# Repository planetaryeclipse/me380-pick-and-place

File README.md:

# me380-pick-and-place
Repository to contain documentation, firmware, and controls for the ME 380 pick and place robot.

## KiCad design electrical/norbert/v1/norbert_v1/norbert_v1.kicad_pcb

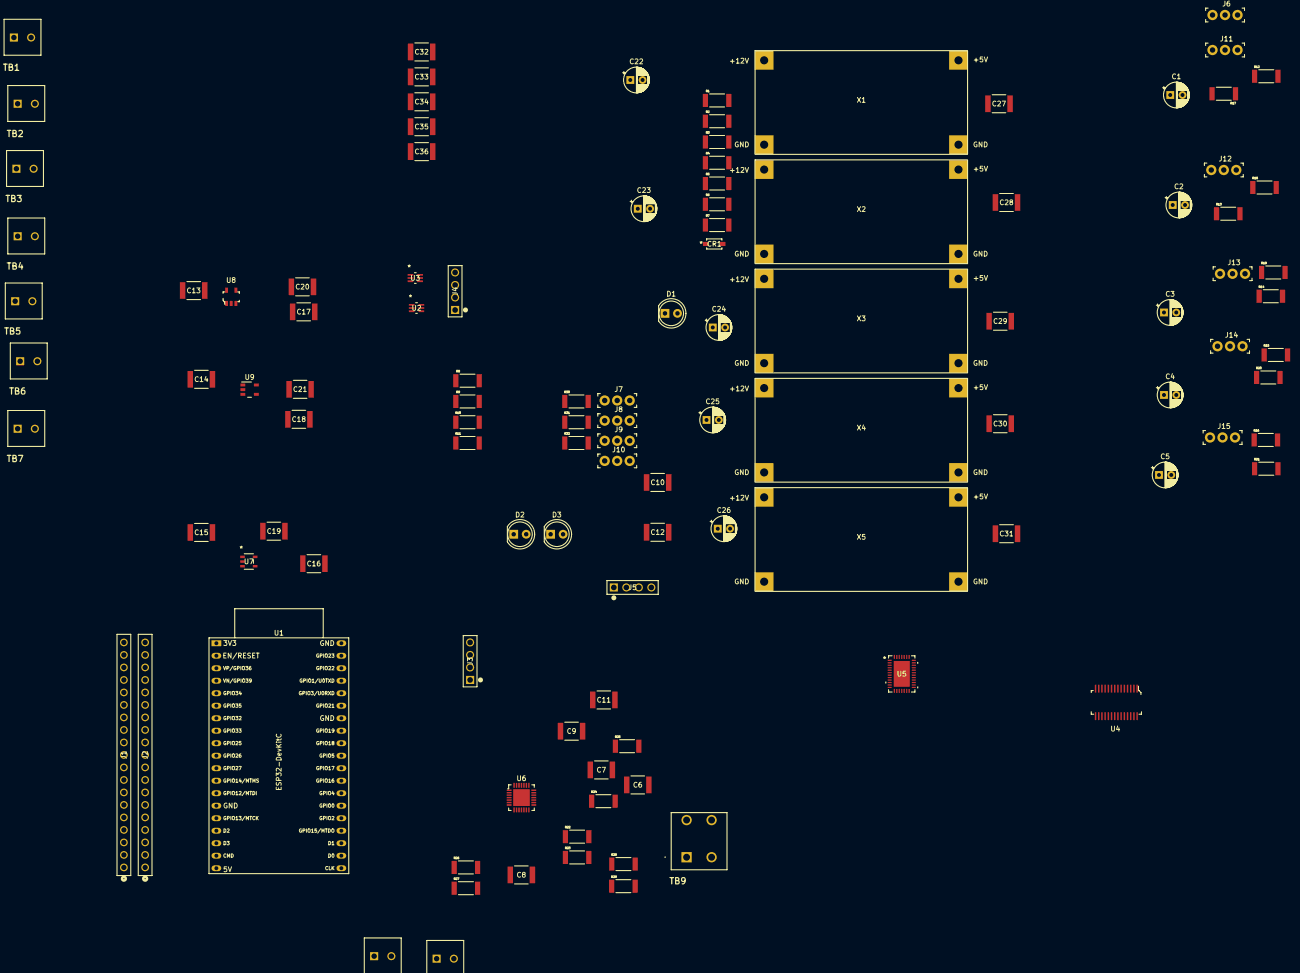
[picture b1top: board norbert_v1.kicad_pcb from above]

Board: 2 copper layers, 111 parts (0 on the bottom side), 99 nets, no tracks yet.

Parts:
C1, C2, C3, C4, C5: 15u; CP_Radial_D5.0mm_P2.50mm
C6, C8: 0.22u; CAP_CC1812_YAG
C7, C9, C12: 0.1u; CAP_CC1812_YAG
C10, C15, C19, C20, C21: 10u; CAP_CC1812_YAG
C11, C32, C33, C34, C35, C36: 100u; CAP_CC1812_YAG
C13, C14: 1u; CAP_CC1812_YAG
C16, C17, C18: 10n; CAP_CC1812_YAG
C22, C23, C24, C25, C26: 100u; CP_Radial_D5.0mm_P2.50mm
C27, C28, C29, C30, C31: 100n; CAP_CC1812_YAG
CR1: MBR0540-TP; SOD-123_MCC
D1: O_LED; LED_D5.0mm
D2: G_LED; LED_D5.0mm
D3: R_LED; LED_D5.0mm
J1, J2: PPTC191LFBN-RC; CONN19_PPTC191LFBN-RC_SUL
J3, J4, J5: 61300411121; CONN_61300411121_WRE
J6, J7, J8, J9, J10, J11, J12, J13, J14, J15: 61300311121; PinHeader_1x3_P2.54_Drill1.1mm
R1, R2, R3, R4, R6, R7, R24, R30, R31, R32: 10k; RESC5025X65N
R5, R8, R9, R10, R11: 100; RESC5025X65N
R12, R13, R14, R15, R16, R17, R18, R19, R20, R21, R28, R29: 0.1; RESC5025X65N
R22: 12k; RESC5025X65N
R23: 910; RESC5025X65N
R25: 5k; RESC5025X65N
R26: 2.74k; RESC5025X65N
R27: 22k; RESC5025X65N
TB1, TB2, TB3, TB4, TB5, TB6, TB7, TB8, TB10: PHOENIX_CONT_2POS_5442248; 5442248
TB9: PHOENIX_CONT_2POS_1730502; 1730502
U1: ESP32-DevKitC
U2, U3: SN74LVC1T45DCKR; DCK6
U4: PCA9685PW_112; TSSOP-28_W4.40mm
U5: LTC2497CUHF-PBF; QFN_UHF-PBF_ADI
U6: A4988SETTR-T; VFQFN-28-1EP_5x5mm
U7: ADP1711AUJZ-0.75R7; UJ_5_ADI
U8: LP2985-33DBVR; SOT-753
U9: LP2985-50DBVR; DBV0005A_N
X1, X2, X3, X4, X5: YIZHET_LM2596_VREG

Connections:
+0.75V: C19.2, U5.29 (REF+), U7.5 (OUT)
+3V3: C6.1, C10.1, C12.1, C21.1, J3.1, R3.1, R7.1, R22.1, R25.1, U2.1 (VCCA), U3.1 (VCCA), U4.28 (VDD), U5.28 (VCC), U6.15 (VDD), U9.5 (VOUT)
+5V: C15.1, C20.1, CR1.2, J4.1, U2.6 (VCCB), U3.6 (VCCB), U7.1 (IN), U7.3 (EN), U8.5 (VOUT)
+5V_A: C1.1, C27.1, C32.2, J6.2, J11.2, X1.3 (OUT+)
+5V_B: C2.1, C28.1, C33.2, J7.2, J12.2, X2.3 (OUT+)
+5V_C: C3.1, C29.1, C34.2, J8.2, J13.2, X3.3 (OUT+)
+5V_D: C4.1, C30.1, C35.2, J9.2, J14.2, X4.3 (OUT+)
+5V_E: C5.1, C31.1, C36.2, J10.2, J15.2, X5.3 (OUT+)
+12V: C9.2, C11.1, C13.1, C14.1, C22.2, C23.2, C24.2, C25.2, C26.2, TB9.1 (Pos), U6.22 (VBB1), U6.28 (VBB2), U8.1 (VIN), U8.3 (ON/~OFF), U9.1 (VIN), U9.3 (ON/~OFF), X1.1 (IN+), X2.1 (IN+), X3.1 (IN+), X4.1 (IN+), X5.1 (IN+)
GPIO_3V3: J1.19, TB1.1 (Pos), TB2.1 (Pos), TB3.1 (Pos), TB4.1 (Pos), TB5.1 (Pos), TB6.1 (Pos), TB7.1 (Pos), U1.1 (3V3)
GPIO_5V: CR1.1, J1.1, U1.19 (5V)
GPIO_CLK: J2.1, U1.20 (SD_CLK/GPIO6)
GPIO_CMD: J1.2, U1.18 (CMD)
GPIO_EN: J1.18, U1.2 (CHIP_PU)
GPIO_GND: C1.2, C2.2, C3.2, C4.2, C5.2, C6.2, C8.2, C10.2, C11.2, C12.2, C13.2, C14.2, C15.2, C16.2, C17.2, C18.2, C19.1, C20.2, C21.2, C22.1, C23.1, C24.1, C25.1, C26.1, C27.2, C28.2, C29.2, C30.2, C31.2, C32.1, C33.1, C34.1, C35.1, C36.1, D1.1 (K), D2.1 (K), D3.1 (K), J1.6, J2.13, J2.19, J3.2, J4.4, J5.2, J5.4, R1.2, R2.2, R4.2, R6.2, R12.2, R13.2, R14.2, R15.2, R16.2, R17.2, R18.2, R19.2, R20.2, R21.2, R24.2, R26.1, R28.1, R29.1, R30.1, R31.2, R32.2, TB9.2 (Pos), U1.14 (GND), U1.32 (GND), U1.38 (GND), U2.2 (GND), U3.2 (GND), U4.1 (A0), U4.2 (A1), U4.3 (A2), U4.4 (A3), U4.5 (A4), U4.14 (VSS), U4.24 (A5), U4.25 (EXTCLK), U5.1 (GND), U5.4 (GND), U5.6 (GND), U5.7 (COM), U5.30 (REF-), U5.31 (GND), U5.32 (GND), U5.33 (GND), U5.34 (GND), U5.35 (fO), U5.39 (GND), U6.3 (GND), U6.18 (GND), U6.29 (GND_PAD), U7.2 (GND), U8.2 (GND), U9.2 (GND), X1.2 (IN-), X1.4 (OUT-), X2.2 (IN-), X2.4 (OUT-), X3.2 (IN-), X3.4 (OUT-), X4.2 (IN-), X4.4 (OUT-), X5.2 (IN-), X5.4 (OUT-)
GPIO_IO0: J2.6, U1.25 (GPIO0/BOOT/ADC2_CH1)
GPIO_IO2: J2.5, R5.2, U1.24 (ADC2_CH2/GPIO2)
GPIO_IO4: J2.7, TB7.2 (Pos), U1.26 (ADC2_CH0/GPIO4)
GPIO_IO5: J2.10, U1.29 (GPIO5), U4.23 (~OE)
GPIO_IO12: J1.7, U1.13 (MTDI/GPIO12/ADC2_CH5), U6.10 (MS2)
GPIO_IO13: J1.5, U1.15 (MTCK/GPIO13/ADC2_CH4), U6.11 (MS3)
GPIO_IO14: J1.8, U1.12 (MTMS/GPIO14/ADC2_CH6), U6.9 (MS1)
GPIO_IO15: J2.4, R3.2, U1.23 (MTDO/GPIO15/ADC2_CH3)
GPIO_IO16: J2.8, TB6.2 (Pos), U1.27 (GPIO16)
GPIO_IO17: J2.9, TB1.2 (Pos), U1.28 (GPIO17)
GPIO_IO18: J2.11, U1.30 (GPIO18), U3.3 (A)
GPIO_IO19: J2.12, U1.31 (GPIO19), U2.3 (A)
GPIO_IO21: J2.14, J3.4, U1.33 (GPIO21), U4.27 (SDA), U5.3 (SDA)
GPIO_IO22: J2.17, J3.3, U1.36 (GPIO22), U4.26 (SCL), U5.2 (SCL)
GPIO_IO23: J2.18, TB2.2 (Pos), U1.37 (GPIO23)
GPIO_IO25: J1.11, U1.9 (DAC_1/ADC2_CH8/GPIO25), U6.16 (STEP)
GPIO_IO26: J1.10, U1.10 (DAC_2/ADC2_CH9/GPIO26), U6.19 (DIR)
GPIO_IO27: J1.9, U1.11 (ADC2_CH7/GPIO27), U6.2 (~ENABLE)
GPIO_IO32: J1.13, U1.7 (32K_XP/GPIO32/ADC1_CH4), U6.12 (~RES)
GPIO_IO33: J1.12, R25.2, U1.8 (32K_XN/GPIO33/ADC1_CH5), U6.14 (~SLEEP)
GPIO_IO34: J1.15, R1.1, TB4.2 (Pos), U1.5 (VDET_1/GPIO34/ADC1_CH6)
GPIO_IO35: J1.14, R2.1, TB5.2 (Pos), U1.6 (VDET_2/GPIO35/ADC1_CH7)
GPIO_RXDO: J2.15, U1.34 (U0RXD/GPIO3)
GPIO_SD0: J2.2, U1.21 (SD_DATA0/GPIO7)
GPIO_SD1: J2.3, U1.22 (SD_DATA1/GPIO8)
GPIO_SD2: J1.4, U1.16 (SD_DATA2/GPIO9)
GPIO_SD3: J1.3, U1.17 (SD_DATA3/GPIO10)
GPIO_SENSOR_VN: J1.16, R4.1, TB3.2 (Pos), U1.4 (SENSOR_VN/GPIO39/ADC1_CH3)
GPIO_SENSOR_VP: J1.17, U1.3 (SENSOR_VP/GPIO36/ADC1_CH0)
GPIO_TXDO: J2.16, U1.35 (U0TXD/GPIO1)
unnamed: D1.2 (A), R5.1
unnamed: D2.2 (A), R8.2
unnamed: D3.2 (A), R11.2
unnamed: J5.1, R9.2
unnamed: J5.3, R10.2
unnamed: R22.2, R23.1
unnamed: R26.2, R27.1
unnamed: TB8.1 (Pos), U6.24 (OUT1A)
unnamed: TB8.2 (Pos), U6.21 (OUT1B)
unnamed: TB10.1 (Pos), U6.26 (OUT2A)
unnamed: TB10.2 (Pos), U6.1 (OUT2B)
unnamed: J4.2, U2.4 (B)
unnamed: R7.2, U2.5 (DIR)
unnamed: J4.3, U3.4 (B)
unnamed: R6.1, U3.5 (DIR)
unnamed: J11.1, U4.6 (LED0)
unnamed: J6.1, U4.7 (LED1)
unnamed: J12.1, U4.8 (LED2)
unnamed: J7.1, U4.9 (LED3)
unnamed: J13.1, U4.10 (LED4)
unnamed: J8.1, U4.11 (LED5)
unnamed: J14.1, U4.12 (LED6)
unnamed: J9.1, U4.13 (LED7)
unnamed: J15.1, U4.15 (LED8)
unnamed: J10.1, U4.16 (LED9)
unnamed: R8.1, U4.17 (LED10)
unnamed: R9.1, U4.18 (LED11)
unnamed: R10.1, U4.19 (LED12)
unnamed: R11.1, U4.20 (LED13)
unnamed: U5.26 (ADCINN), U5.27 (MUXOUTN)
unnamed: U5.24 (MUXOUTP), U5.25 (ADCINP)
unnamed: R30.2, U5.36 (CA0)
unnamed: R31.1, U5.37 (CA1)
unnamed: R32.1, U5.38 (CA2)
unnamed: J11.3, R17.1, U5.8 (CH0)
unnamed: J6.3, R12.1, U5.9 (CH1)
unnamed: J12.3, R18.1, U5.10 (CH2)
unnamed: J7.3, R13.1, U5.11 (CH3)
unnamed: J13.3, R19.1, U5.12 (CH4)
unnamed: J8.3, R14.1, U5.13 (CH5)
unnamed: J9.3, J14.3, R15.1, R20.1, U5.14 (CH6), U5.15 (CH7)
unnamed: J15.3, R21.1, U5.16 (CH8)
unnamed: J10.3, R16.1, U5.17 (CH9)
unnamed: R29.2, U5.18 (CH10), U6.23 (SENSE1)
unnamed: R28.2, U5.19 (CH11), U6.27 (SENSE2)
unnamed: C7.1, U6.4 (CP1)
unnamed: C7.2, U6.5 (CP2)
unnamed: R23.2, R24.1, U6.17 (REF)
unnamed: R27.2, U6.13 (ROSC)
unnamed: C9.1, U6.6 (VCP)
unnamed: C8.1, U6.8 (VREG)
unnamed: C16.1, U7.4 (BYP)
unnamed: C17.1, U8.4 (BYP)
unnamed: C18.1, U9.4 (BYP)

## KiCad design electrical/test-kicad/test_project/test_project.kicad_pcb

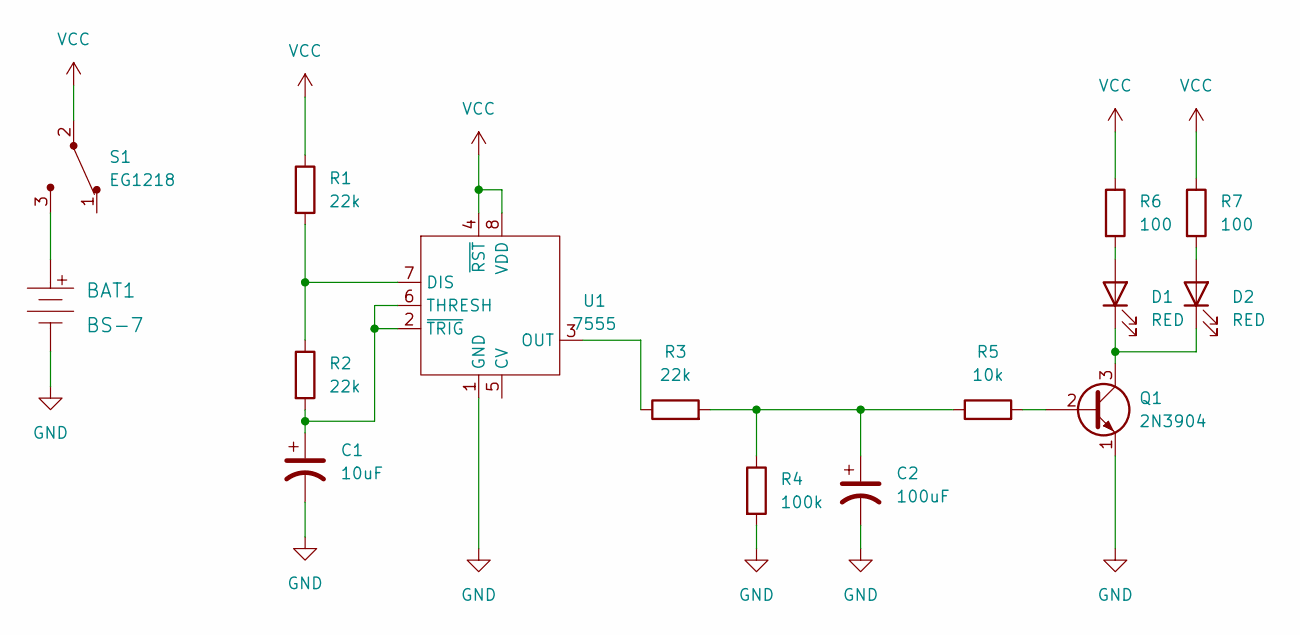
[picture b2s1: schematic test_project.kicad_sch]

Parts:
BAT1: BS-7; Battery_Holder_Coin_2032_BS-7; MPN BS-7; Digi-Key_PN BS-7-ND
C1: 10uF; CP_Radial_D5.0mm_P2.00mm
C2: 100uF; CP_Radial_D6.3mm_P2.50mm
D1, D2: RED; LED_D3.0mm
Q1: 2N3904; TO-92-3
R1, R2, R3: 22k; R_Axial_DIN0207_L6.3mm_D2.5mm_P7.62mm_Horizontal
R4: 100k; R_Axial_DIN0207_L6.3mm_D2.5mm_P7.62mm_Horizontal
R5: 10k; R_Axial_DIN0207_L6.3mm_D2.5mm_P7.62mm_Horizontal
R6, R7: 100; R_Axial_DIN0207_L6.3mm_D2.5mm_P7.62mm_Horizontal
S1: EG1218; Switch_Slide_11.6x4mm_EG1218; MPN EG1218; Digi-Key_PN EG1903-ND
U1: 7555; ICM7555-PDIP

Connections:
GND: BAT1.Neg, C1.2, C2.2, Q1.1 (E), R4.2, U1.1 (GND)
unnamed: BAT1.Pos, S1.3
unnamed: C2.1, R3.2, R4.1, R5.1
unnamed: D1.2 (A), R6.2
unnamed: D1.1 (K), D2.1 (K), Q1.3 (C)
unnamed: D2.2 (A), R7.2
unnamed: Q1.2 (B), R5.2
unnamed: R1.2, R2.1, U1.7 (DIS)
unnamed: R3.1, U1.3 (OUT)
unnamed: C1.1, R2.2, U1.2 (~TRIG), U1.6 (THRESH)
VCC: R1.1, R6.1, R7.1, S1.2, U1.4 (~RST), U1.8 (VDD)

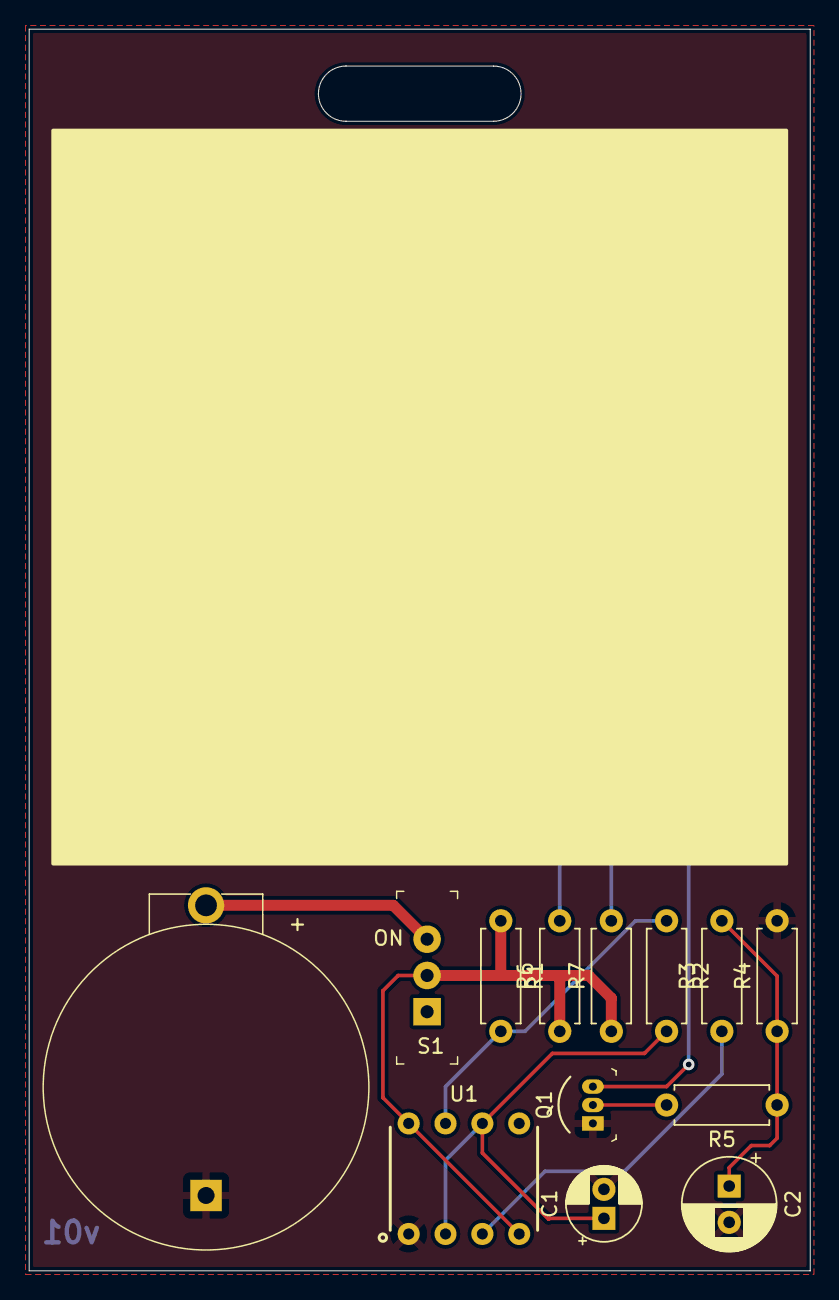
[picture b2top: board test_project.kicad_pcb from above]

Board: 2 copper layers, 53.8 x 85.6 mm, 15 parts (0 on the bottom side), 11 nets.

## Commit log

2023-09-15 Add testing ESP32 code for LED
    Add .gitignore and remove tracking of builds
2023-09-15 Add servo testing control
2023-09-16 Add integration of encoder
2023-09-16 Reorganize firmware testing directory
2023-09-16 Add support for TB6600 stepper motor driver
2023-10-30 Add demo firmware for construction check 1
2023-10-30 Separate testing firmware to separate directory
2023-10-30 Add initial firmware with blink
2023-11-02 Added color sensor I2C interface code
2023-11-02 Added GPIO ISRs for limit switches
2023-11-02 Added ultrasonic sensor
2023-11-04 Added stepper control
2023-11-05 Added current sensing from ACS723
2023-11-05 Added servo motors
2023-11-06 Refactored driver code to separate files
2023-11-06 Added power monitor for reset/fault state
2023-11-07 Fixed ultrasonic interfacing bug
2023-11-12 Add r3 of PCB design
2023-11-12 Added UART comms for host commands
2023-11-16 Configured servo motors to achieve synchronized lifting
2023-11-16 Increased height of lifting mechanism
2023-11-16 Changed servo driver to require enable
2023-11-16 Fixed a typo on a pin name
2023-12-05 Add changes made for final demo
2023-12-05 Add remaining changes for electrical design

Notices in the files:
electrical/test-kicad/test_project/test_project.kicad_pcb:
creativecommons.org/license/by/4.0
License: CC BY 4.0
